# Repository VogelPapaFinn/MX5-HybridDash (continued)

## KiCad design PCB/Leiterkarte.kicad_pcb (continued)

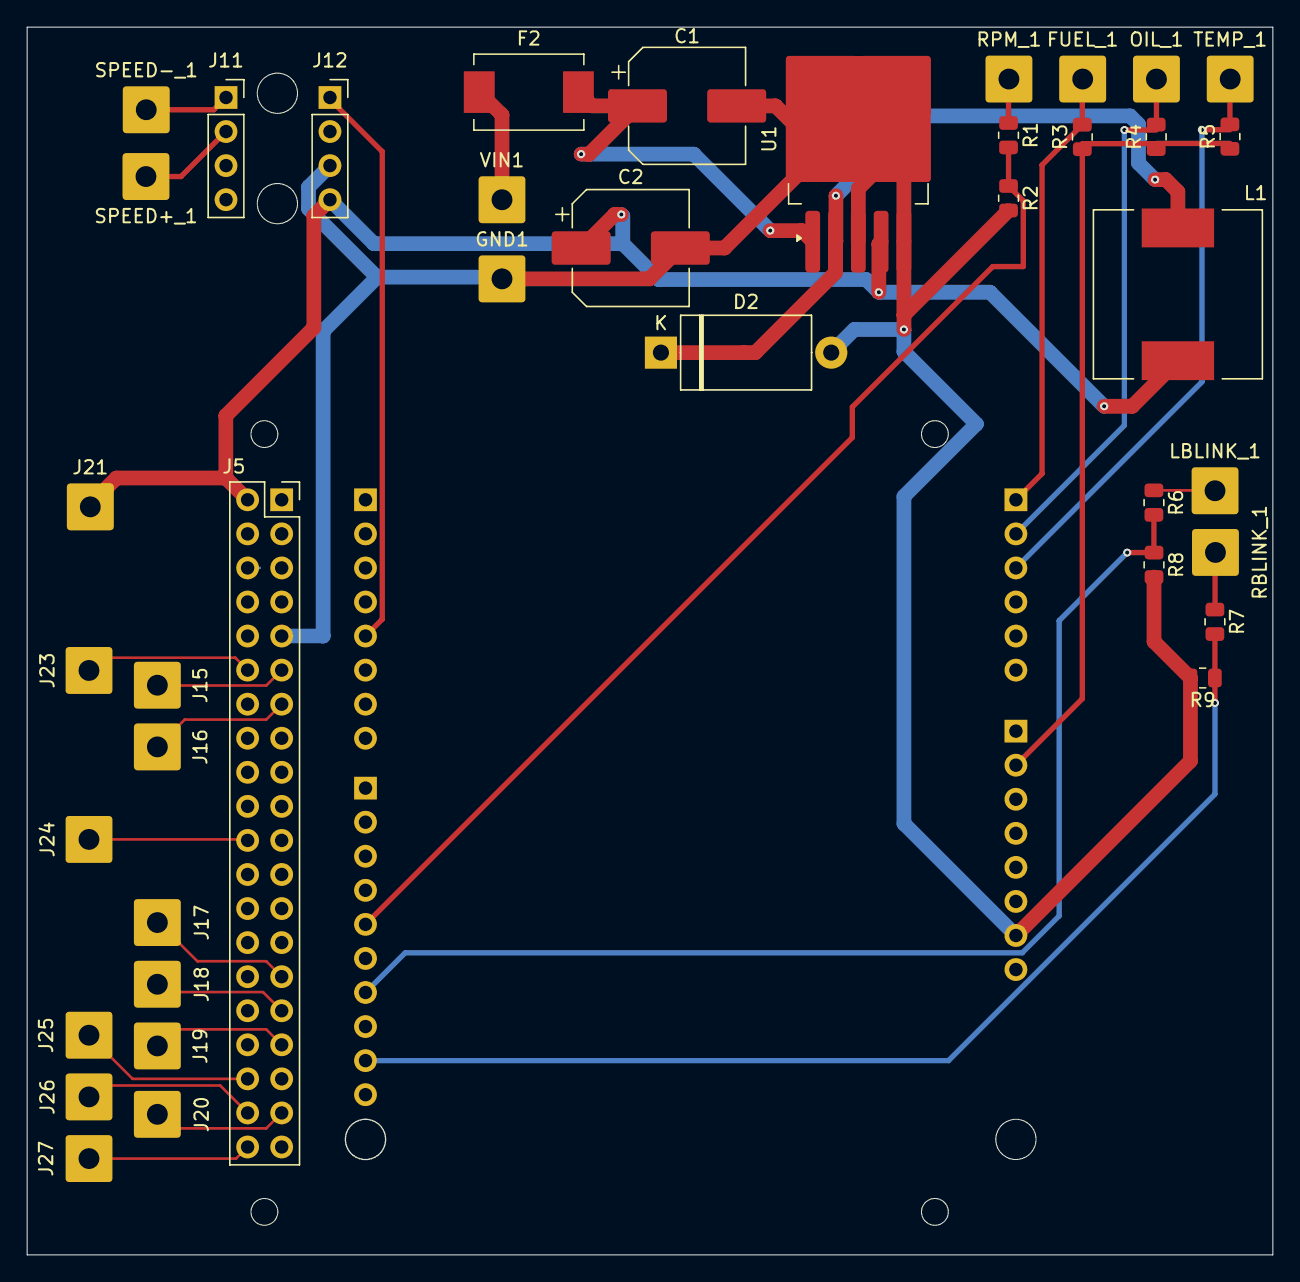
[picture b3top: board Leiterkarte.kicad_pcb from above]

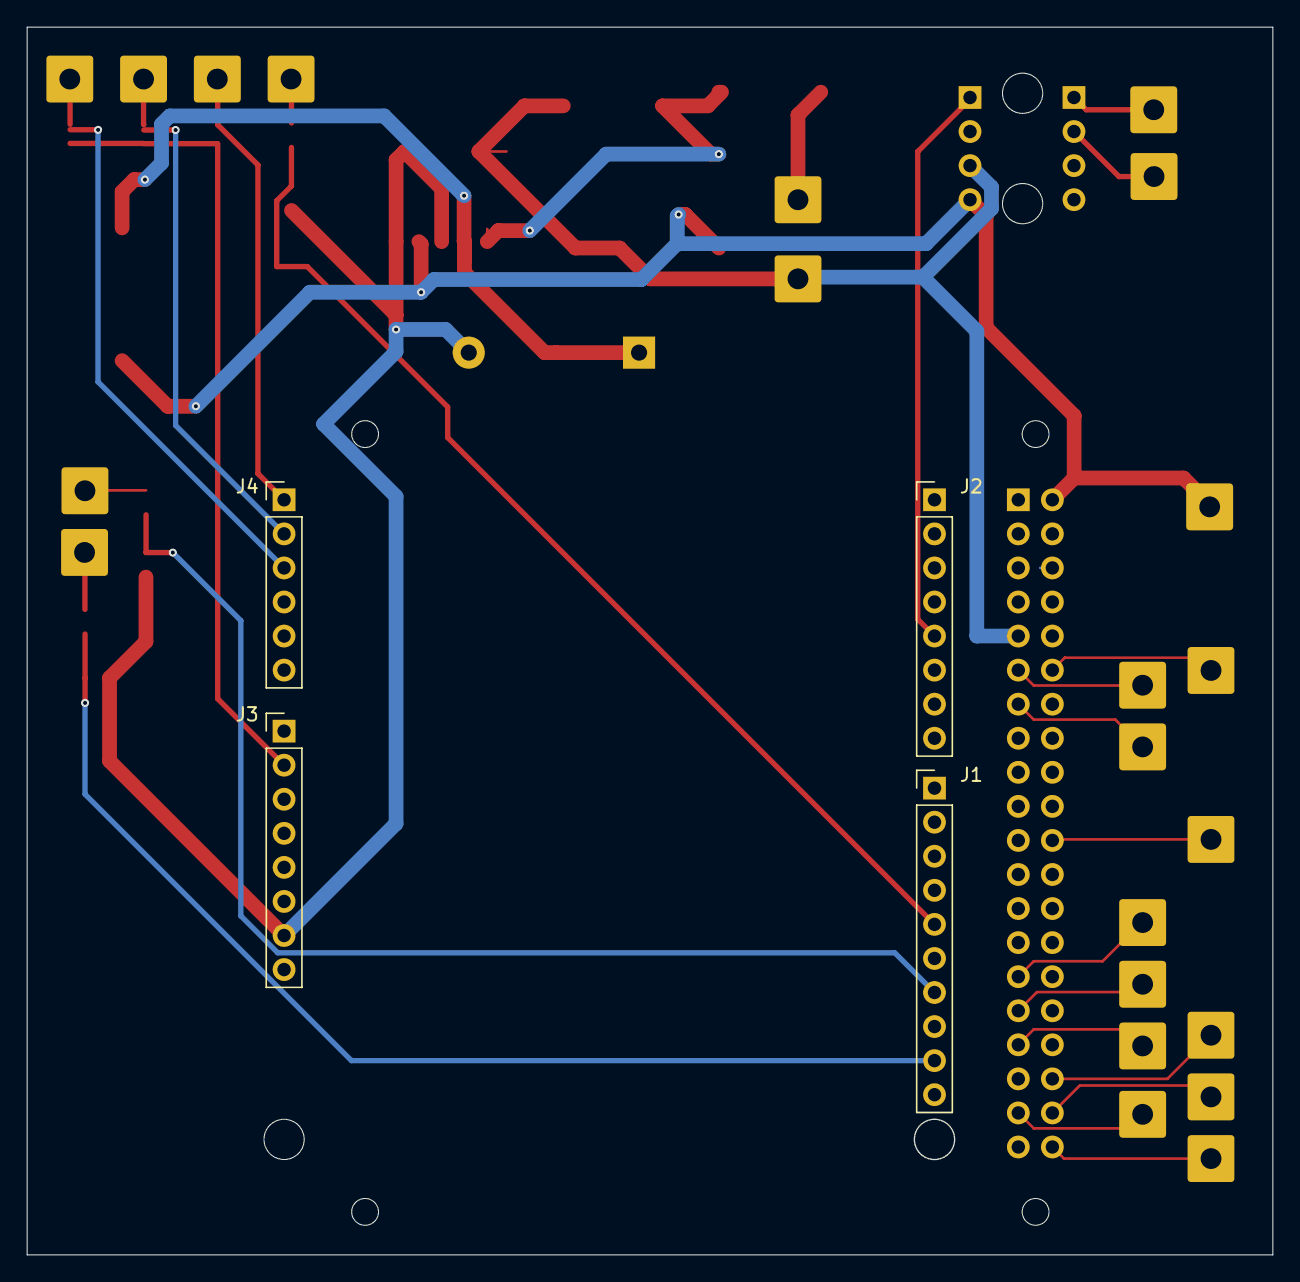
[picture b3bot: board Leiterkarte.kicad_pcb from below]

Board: 2 copper layers, 92.9 x 91.5 mm, 44 parts (4 on the bottom side), 29 nets.

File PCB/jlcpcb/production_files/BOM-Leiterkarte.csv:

Comment,Designator,Footprint,LCSC
ARDUINO_ANLG,J4,PinHeader_1x06_P2.54mm_Vertical,
20k,R1,R_0805_2012Metric,
Conn_01x01_Pin,GND1,SolderWire-0.75sqmm_1x01_D1.25mm_OD3.5mm,
Conn_01x01_Pin,VIN1,SolderWire-0.75sqmm_1x01_D1.25mm_OD3.5mm,
10k,R2,R_0805_2012Metric,
100,R4,R_0805_2012Metric,
Conn_02x20_Odd_Even,J5,PinSocket_2x20_P2.54mm_Vertical,
100,R3,R_0805_2012Metric,
20k,R6,R_0805_2012Metric,
ARDUINO_DIG1,J1,PinHeader_1x10_P2.54mm_Vertical,
ARDUINO_PWR,J3,PinHeader_1x08_P2.54mm_Vertical,
100,R5,R_0805_2012Metric,
ARDUINO_DIG2,J2,PinHeader_1x08_P2.54mm_Vertical,
20k,R7,R_0805_2012Metric,
Conn_01x01_Pin,J17,SolderWire-0.75sqmm_1x01_D1.25mm_OD3.5mm,
Conn_01x01_Pin,J26,SolderWire-0.75sqmm_1x01_D1.25mm_OD3.5mm,
470uF 16V,C2,CP_Elec_8x10.5,
Conn_01x01_Pin,J16,SolderWire-0.75sqmm_1x01_D1.25mm_OD3.5mm,
Conn_01x04_Socket,J12,PinSocket_1x04_P2.54mm_Vertical,
Conn_01x01_Pin,J20,SolderWire-0.75sqmm_1x01_D1.25mm_OD3.5mm,
Conn_01x01_Pin,FUEL_1,SolderWire-0.75sqmm_1x01_D1.25mm_OD3.5mm,
10k,R9,R_0805_2012Metric,
Conn_01x01_Pin,RPM_1,SolderWire-0.75sqmm_1x01_D1.25mm_OD3.5mm,
LM2576HVS-5,U1,TO-263-5_TabPin3,
100uF 50V,C1,CP_Elec_8x10.5,
Conn_01x01_Pin,J19,SolderWire-0.75sqmm_1x01_D1.25mm_OD3.5mm,
Conn_01x01_Pin,OIL_1,SolderWire-0.75sqmm_1x01_D1.25mm_OD3.5mm,
Conn_01x01_Pin,TEMP_1,SolderWire-0.75sqmm_1x01_D1.25mm_OD3.5mm,
Conn_01x01_Pin,LBLINK_1,SolderWire-0.75sqmm_1x01_D1.25mm_OD3.5mm,
Conn_01x01_Pin,J15,SolderWire-0.75sqmm_1x01_D1.25mm_OD3.5mm,
Conn_01x01_Pin,RBLINK_1,SolderWire-0.75sqmm_1x01_D1.25mm_OD3.5mm,
Conn_01x01_Pin,J23,SolderWire-0.75sqmm_1x01_D1.25mm_OD3.5mm,
1N5819,D2,D_DO-27_P12.70mm_Horizontal,
Conn_01x01_Pin,J21,SolderWire-0.75sqmm_1x01_D1.25mm_OD3.5mm,
Conn_01x01_Pin,J24,SolderWire-0.75sqmm_1x01_D1.25mm_OD3.5mm,
Conn_01x01_Pin,J27,SolderWire-0.75sqmm_1x01_D1.25mm_OD3.5mm,
3.5A,F2,Fuse_Bourns_MF-SM_7.98x5.44mm,
10k,R8,R_0805_2012Metric,
Conn_01x01_Pin,J25,SolderWire-0.75sqmm_1x01_D1.25mm_OD3.5mm,
Conn_01x04_Socket,J11,PinSocket_1x04_P2.54mm_Vertical,
100myH,L1,L_12x12mm_H8mm,
Conn_01x01_Pin,J18,SolderWire-0.75sqmm_1x01_D1.25mm_OD3.5mm,

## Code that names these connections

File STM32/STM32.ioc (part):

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Mcu.Name=STM32H743VITx
Mcu.Package=LQFP100
Mcu.UserName=STM32H743VITx
PA0.GPIOParameters=GPIO_Label
PA0.GPIO_Label=RPM
PA0.Signal=S_TIM2_CH1_ETR
PA1.GPIOParameters=GPIO_Label
PA1.GPIO_Label=Speed
PA1.Signal=S_TIM2_CH2
PA13\ (JTMS/SWDIO).Mode=Serial_Wire
PA13\ (JTMS/SWDIO).Signal=DEBUG_JTMS-SWDIO
PA14\ (JTCK/SWCLK).Mode=Serial_Wire
PA14\ (JTCK/SWCLK).Signal=DEBUG_JTCK-SWCLK
PA2.GPIOParameters=GPIO_Label
PA2.GPIO_Label=TempS1
PA2.Signal=ADCx_INP14
PA3.GPIOParameters=GPIO_Label
PA3.GPIO_Label=TempS2
PA3.Signal=ADCx_INP15
PA4.GPIOParameters=GPIO_Label
PA4.GPIO_Label=Fuel
PA4.Signal=ADCx_INP18
PA5.GPIOParameters=GPIO_Label
PA5.GPIO_Label=Oil
PA5.Signal=ADCx_INP19
PA6.GPIOParameters=GPIO_Label
PA6.GPIO_Label=Water
PA6.Signal=ADCx_INP3
PA7.GPIOParameters=GPIO_PuPd,GPIO_Label
PA7.GPIO_Label=LIndicator
PA7.GPIO_PuPd=GPIO_PULLDOWN
PA7.Signal=GPIO_Input
PB12.GPIOParameters=GPIO_Label
PB12.GPIO_Label=YLed
PB12.Signal=GPIO_Output
PB13.GPIOParameters=GPIO_Label
PB13.GPIO_Label=OLed
PB13.Signal=GPIO_Output
PB14.GPIOParameters=GPIO_Label
PB14.GPIO_Label=GLed
PB14.Signal=GPIO_Output
PB15.GPIOParameters=GPIO_PuPd,GPIO_Label
PB15.GPIO_Label=Button3
PB15.GPIO_PuPd=GPIO_PULLDOWN
PB15.Signal=GPIO_Input
PB3\ (JTDO/TRACESWO).Mode=TX_Only_Simplex_Unidirect_Master
PB3\ (JTDO/TRACESWO).Signal=SPI1_SCK
PB4\ (NJTRST).GPIOParameters=GPIO_Label
PB4\ (NJTRST).GPIO_Label=BL
PB4\ (NJTRST).Signal=S_TIM3_CH1
PB5.GPIOParameters=GPIO_Label
PB5.GPIO_Label=RST_SPI2
PB5.Signal=GPIO_Output
PB6.GPIOParameters=GPIO_Label
PB6.GPIO_Label=DC_SPI2
PB6.Signal=GPIO_Output
PB7.GPIOParameters=GPIO_Label
PB7.GPIO_Label=CS_SPI2
PB7.Signal=GPIO_Output
PC10.Mode=SD_4_bits_Wide_bus
PC10.Signal=SDMMC1_D2
PC11.Mode=SD_4_bits_Wide_bus
PC11.Signal=SDMMC1_D3
PC12.Mode=SD_4_bits_Wide_bus
PC12.Signal=SDMMC1_CK
PC4.GPIOParameters=GPIO_PuPd,GPIO_Label
PC4.GPIO_Label=RIndicator
PC4.GPIO_PuPd=GPIO_PULLDOWN
PC4.Signal=GPIO_Input
PC8.Mode=SD_4_bits_Wide_bus
PC8.Signal=SDMMC1_D0
PC9.Mode=SD_4_bits_Wide_bus
PC9.Signal=SDMMC1_D1
PD10.GPIOParameters=GPIO_Label
PD10.GPIO_Label=FanCtrl
PD10.Signal=GPIO_Output
PD2.Mode=SD_4_bits_Wide_bus
PD2.Signal=SDMMC1_CMD
PD4.GPIOParameters=GPIO_Label
PD4.GPIO_Label=RST_SPI3
PD4.Signal=GPIO_Output
PD5.GPIOParameters=GPIO_Label
PD5.GPIO_Label=DC_SPI3
PD5.Signal=GPIO_Output
PD6.GPIOParameters=GPIO_Label
PD6.GPIO_Label=CS_SPI3
PD6.Signal=GPIO_Output
PD7.Mode=TX_Only_Simplex_Unidirect_Master
PD7.Signal=SPI1_MOSI
PD8.GPIOParameters=GPIO_Label,GPIO_PuPd
PD8.GPIO_Label=Button2
PD8.GPIO_PuPd=GPIO_PULLDOWN
PD8.Signal=GPIO_Input
PD9.GPIOParameters=GPIO_Label,GPIO_PuPd
PD9.GPIO_Label=Button1
PD9.GPIO_PuPd=GPIO_PULLDOWN
PD9.Signal=GPIO_Input
PE2.GPIOParameters=GPIO_Label
PE2.GPIO_Label=RST_SPI1
PE2.Signal=GPIO_Output
PE3.GPIOParameters=GPIO_Label
PE3.GPIO_Label=DC_SPI1
PE3.Signal=GPIO_Output
PE4.GPIOParameters=GPIO_Label
PE4.GPIO_Label=CS_SPI1
PE4.Signal=GPIO_Output
RCC.HSE_VALUE=25000000
RCC.SYSCLKFreq_VALUE=480000000
RCC.SYSCLKSource=RCC_SYSCLKSOURCE_PLLCLK
board=custom

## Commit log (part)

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2024-08-14 Initial Commit v1
2024-08-14 Initial README commit
2024-08-14 Removed unneeded file
2024-08-18 Updated component selection; Updated some footprints; Added .csv file in the export folder of the PCB that contains parts from DigiKey
2024-08-25 Added 2x Temperature Sensors; Updated wrong GPIO connections in schematic; Set Button input GPIOs to Pull-Down; LED circuits need to be corrected
2024-08-30 add resistors for status LEDs
2024-08-30 Switched from L6981N50DR to TPS5430DDAR
2024-08-31 Replaced some global labels with power net(s); Added warning label for missing component
2024-09-07 Fixed wrong link in README.md
2024-09-20 Finalized circuit design; First try of PCB layout (FAILED)
2024-09-20 Finalized circuit design; Added PCB layout
2024-09-20 Added ground pours
2024-09-21 Added 3D models for the JST connectors, MSD-1-A, MOSFET and MAX9924
2024-09-21 Moved component names on the PCB name; Rotated MOSFET
2024-09-21 Replaced Inductor L1; Replaced MOSFET; Places some vias in the ground pours
2024-09-21 Added list of trustworthy manufacturers; Replaced inductor L1
2024-09-21 Fixed missing 3D model
2024-09-22 Replaced Speed- and Speed+ solder faces with JST SH connector
2024-09-23 Replaced capacitor Cout2 and moved it to other side of the PCB;Updated some resistor footprints (to 0805);Some other stuff I forgot but similar :)
2024-09-29 Replaced STM32 with ESP32; Addec circuitry for ESP32; Removed LEDs; Added USB-C for flashing
2024-10-12 Changed PCB design completely; Upgraded 3.3V regulator to 1.5A version; Removed no more needed libaries
2024-10-15 Changed position of IGN M3 hole;Changed M3 hole diameter from 3.2 to 3.5
2024-10-15 Replaced Fuse;Updated BOM file
2024-10-15 Added backup files
2024-10-16 Added pulldown resistors for the buttons;Changed input GPIof button 3;Replaced a few capacitors (BOM); Put temperature sensors on the 3.3V line
2024-10-16 Changed buttons footprint; Changed buttons LCSC component due to shortage; Updated components rotation for JLCPCB;
2024-10-16 Did some stuff but I forgot what. Was just some small stuff, probably nothing important
2024-10-30 Created firmware project
2024-11-13 Initializing Firmware Project
2024-11-13 Added esp-idf submodule
2024-11-13 Changed submodule version to v5.4
2024-11-13 Added .gitignore
2024-11-13 Setup firmware project; Moved esp-idf submodule
2024-12-11 Basic tests finished: Got SDCard working, LVGL & SPI display, SPIRAM and FLASH
2024-12-11 Fixed missing dependency; Fixed small display bug
2024-12-17 Added debugging deps (WIP);Updated partitions table;Implemented basic FileManager operations;Implemented basic Logging operations
2024-12-23 Replaced oil and fuel 'pre resistor' to 240 ohms; Replaced water temp 'pre resistor' to 3k ohms; Implemented basic functionality of SensorManager (WIP); Implemented simple log-level feature
2025-01-05 Implemented measurement of speed and rpm; The speed hz is measured but is not yet converted to actual kmh/mph
2025-01-05 Implemented reading of internal (on-board) temperature sensor
2025-01-13 Fixed crash when no SDCard was inserted
2025-01-13 WIP GUI system; The three displays and LVGL gets initialized
2025-02-14 Implemented 3 screens: Speedometer, RPM, Fuel & Temp; Fixed issue where the display showed random colored pixels at startup;
2025-03-08 PCB Version 2.1
2025-03-08 Fixed wrong SPI label
2025-03-18 Redone Schematics for better readability (the circuitry didnt change
2025-03-21 Applied recommendations from my coworker; Fixed badly placed filter caps; Added flyback diode to fan circuit; Applied larger grid and some spacing to the schematics; And some other small adjustments
2025-03-23 Changed some resistor and capacitor values;Added additional input electrolytic cap;Selected LCSC parts;Added diode footprint;Removed 3.3V power supply and decreased the output of the 5V supply to 3.3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
2025-05-01 Finished v2.1 and preparing v2.2;Removed debugging stuff from the firmware project
2025-11-15 Added esp-idf as submodule
2025-11-15 Refilled README with basic stuff
2025-11-16 Removed idf.bat; Updated submodules; Implemented can bus components with basic transmit/receive functionality
2025-11-23 Updated FW; Added .clang-format for espidf components;Added first few CAN Messages;Readded Logger as component;
2025-12-08 Updated DisplayBoard Firmware; Updated SensorBoard Firmware; Implemented basic statemachine; Changed how the CAN lib works
2025-12-21 Altered CAN messaged; New FW versions
2026-01-04 Updated DisplayBoard and SensorBoard Firmware; Implemented CAN bus recovery request; Removed logger component; Applied clang-tidy rules
2026-01-04 Updated Display and Sensor firmware
2026-01-06 Added firmware version request CAN logic; Added deactivated CAN debugging function; Updated Sensor and Display firmware]
2026-01-09 Reworked CAN system; Removed state machine component; Updated SensorBoard and DisplayBoard firmware
2026-01-10 Cleanup of CAN component
2026-01-10 Updated SensorBoard firmware; Added unregister rx cb function in the CAN
2026-01-10 Changed name of CAN message; Updated Display and Sensor Board firmware
2026-01-11 Changed how the CAN passes rx frames; Fixed NULL pointer exception; Fixed brs = 1 bug
2026-01-17 Fixed a bug where received CAN data was sometimes out of scope; Updated Sensor and Display Board firmware
2026-01-19 Updated Display and Sensor Board firmware
2026-01-31 Reworked Display Board circuitry and layout
2026-02-01 Updated SensorBoard HW
2026-05-02 Added rewritten Filesystem component; Rewritten CAN component; Updated 3D Models, Footprints etc.; Added PDF for KLine protocol (communication with ECU, which is confirmed to be working but not yet i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
2026-05-02 Updated DisplayPCB , SensorBoardPCB and SensorBoardFW submodules
2026-05-08 Changed CAN header structure; Fixed dangling pointer when sending data; Fixed issue where data was send but nothing was received; Updated UI
2026-05-08 Moved the Config class from the SensorBoard FW to the Filesystem component; Fixed issue in the Filesystem component
2026-06-05 Updated CAN Driver; Updated Config File Driver; Updated EEZ Project
2026-06-07 Removed debugging log from CAN driver; Updated Display Firmware; Updated Sensorboard Firmware; Added MX5NB service manual;
2026-06-07 Updated Display Firmware Version
2026-06-12 Fixed racing issue in the CAN driver; Moved Wifi driver to its own espidf component; Updated Display and Sensor Board FW
2026-06-13 Deactivated logging in the CAN driver; Fixed issue in the WifiHost driver; Updated Display & Sensor PCB firmware
2026-06-17 Added image for README.md
2026-06-17 Fixed image
2026-06-17 Added GPLv3 license
2026-06-19 Aktualisieren von README.md
